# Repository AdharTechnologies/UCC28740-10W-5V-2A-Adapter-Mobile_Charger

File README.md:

# UCC28740-10W-5V-2A-Adapter-Mobile_Charger

1. Product page https://www.ti.com/product/UCC28740
2. Datasheet https://www.ti.com/lit/ds/symlink/ucc28740.pdf?ts=1782194478570&ref_url=https%253A%252F%252Fwww.ti.com%252Fproduct%252FUCC28740
3. Reference Design https://www.ti.com/lit/ug/sluual8/sluual8.pdf?ts=1782218864686&ref_url=https%253A%252F%252Fwww.ti.com%252Ftool%252FUCC28740EVM-525

#Note
This design was done for practice purpose it has not been tested

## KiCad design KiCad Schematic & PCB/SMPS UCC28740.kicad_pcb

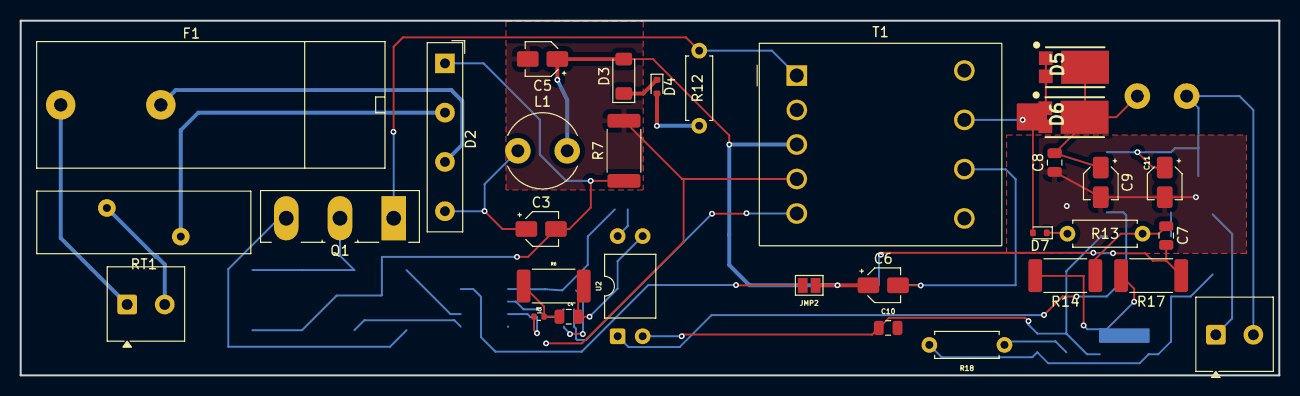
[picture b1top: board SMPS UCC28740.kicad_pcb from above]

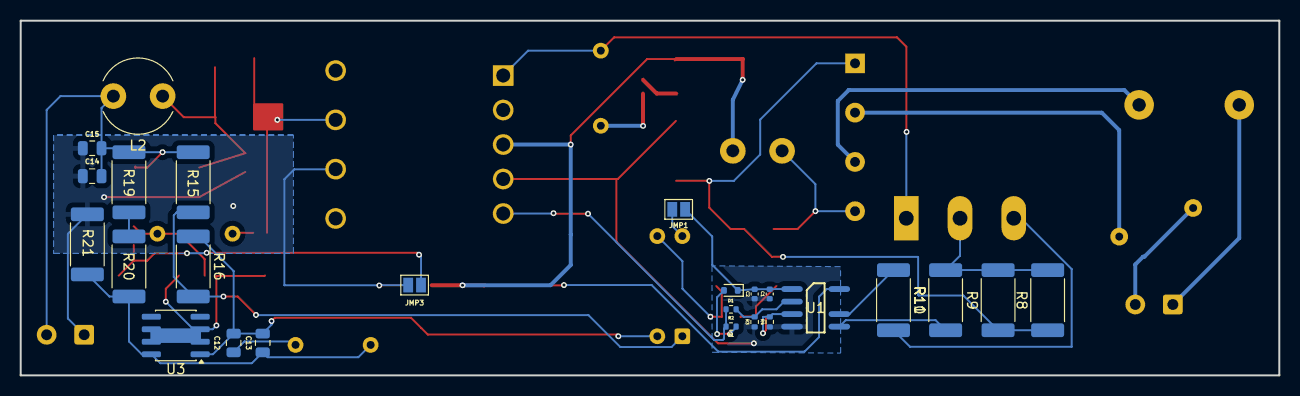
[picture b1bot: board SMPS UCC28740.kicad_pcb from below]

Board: 2 copper layers, 127.7 x 36.0 mm, 55 parts (25 on the bottom side), 35 nets.

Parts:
C1, C2: 2.2uF; C_0402_1005Metric
C3, C5: 6.8uF; CP_Elec_3x5.4
C4: 0.047uF; C_0805_2012Metric
C6: 100pF; CP_Elec_3x5.4
C7, C8, C10, C14, C15: 1uF; C_0805_2012Metric
C9, C11: 270uF; CP_Elec_3x5.4
C12: 4700pF; C_0805_2012Metric
C13: 2700pF; C_0805_2012Metric
D1: 200V,250mA; D_SOD-523
D2: 600V,0.8A; Diode_Bridge_19.0x3.5x10.0mm_P5.0mm
D3: 120V,600W; D_MiniMELF
D4: 1000V,1A; D_SOD-523
D5, D6: SBR10U45SP5-13; POWERDI5
D7: 75V,0.3A; D_SOD-523
F1: 2A,250V; Fuseholder_Cylinder-5x20mm_Bulgin_FX0457_Horizontal_Closed
JMP1, JMP2, JMP3: Jumper_2_Open; SolderJumper-2_P1.3mm_Open_Pad1.0x1.5mm
L1: 220uH; L_Radial_D7.5mm_P5.00mm_Fastron_07P
L2: 1uH; L_Radial_D7.5mm_P5.00mm_Fastron_07P
Q1: STU7NM60N; TO-247-3_Vertical
R1: 24.3; R_0402_1005Metric
R2: 105K; R_0402_1005Metric
R3: 27.4K; R_0402_1005Metric
R4: 22K; R_0402_1005Metric
R5: 0Ω,0.1W; R_0402_1005Metric
R6: 196K; R_2512_6332Metric_Pad1.40x3.35mm_HandSolder
R7: 0Ω, 0.125W; R_2512_6332Metric_Pad1.40x3.35mm_HandSolder
R8, R9: 1.87; R_2512_6332Metric_Pad1.40x3.35mm_HandSolder
R10: 0Ω,0.1W; R_2512_6332Metric_Pad1.40x3.35mm_HandSolder
R11: 1.29K; R_2512_6332Metric_Pad1.40x3.35mm_HandSolder
R12: 49.9; R_Axial_DIN0207_L6.3mm_D2.5mm_P7.62mm_Horizontal
R13: 820; R_Axial_DIN0207_L6.3mm_D2.5mm_P7.62mm_Horizontal
R14, R17: 0Ω, 0.1W; R_2512_6332Metric_Pad1.40x3.35mm_HandSolder
R15: 1.5K; R_2512_6332Metric_Pad1.40x3.35mm_HandSolder
R16: 1K; R_2512_6332Metric_Pad1.40x3.35mm_HandSolder
R18: 140K; R_Axial_DIN0207_L6.3mm_D2.5mm_P7.62mm_Horizontal
R19: 49.9; R_2512_6332Metric_Pad1.40x3.35mm_HandSolder
R20, R21: 42.2K; R_2512_6332Metric_Pad1.40x3.35mm_HandSolder
RT1: 10 Ω; RV_Disc_D21.5mm_W6.1mm_P7.5mm
T1: 560uH; T_Wurth_WE-FB-EE16_8_5
U1: UCC28740D; D0007A_N
U2: LTV‐817A; DIP-4_W10.16mm
U3: TL431D; SOIC-8_3.9x4.9mm_P1.27mm

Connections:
unnamed: C4.1, R6.2, U2.3
unnamed: C4.2, R5.2, R6.1
unnamed: C7.1, R13.2, R14.1
unnamed: C8.2, C9.1, D5.3, D6.3, L2.1
unnamed: C12.1, R18.1
unnamed: D1.2 (A), R1.1
unnamed: C1.1, C2.1, D1.1 (K), JMP1.1 (A), U1.1 (VDD)
unnamed: C3.1, D2.4 (+), L1.1
unnamed: C3.2, D2.1 (-), R7.1, R8.1, R9.1
unnamed: D2.2, RT1.2
unnamed: D2.3, F1.2
unnamed: C5.1, C6.1, D3.2 (A), JMP2.1 (A), L1.2, T1.3
unnamed: D3.1 (K), D4.1 (K)
unnamed: D4.2 (A), R12.1
unnamed: D5.1, D5.2, D6.1, D6.2, D7.2 (A), T1.8
unnamed: D7.1 (K), R13.1
unnamed: C11.1, C14.2, C15.2, L2.2, R15.2, R19.2
unnamed: JMP1.2 (B), U2.4
unnamed: JMP2.2 (B), U1.8 (HV)
unnamed: C7.2, JMP3.1 (A), R17.1
unnamed: Q1.1, R12.2, T1.1
unnamed: Q1.2, R8.2, R9.2, R11.2
unnamed: Q1.3, R10.2
unnamed: R14.2, R17.2, U3.2 (A), U3.3 (A), U3.6 (A), U3.7 (A)
unnamed: R15.1, R16.2, U2.1
unnamed: R19.1, R20.2
unnamed: R11.1, U1.5 (CS)
unnamed: R10.1, U1.6 (DRV)
unnamed: R4.2, R5.1, U1.3 (FB)
unnamed: R2.1, R3.2, U1.2 (VS)
unnamed: C10.1, C12.2, C13.2, R16.1, U2.2, U3.1 (K)
unnamed: C13.1, R18.2, R20.1, R21.2, U3.8 (REF)
PGND: C1.2, C2.2, C5.2, R3.1, R4.1, R7.2, T1.4, U1.4 (GND)
SGND: C6.2, C8.1, C9.2, C10.2, C11.2, C14.1, C15.1, JMP3.2 (B), R21.1, T1.7
VDD: R1.2, R2.2, T1.5

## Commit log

2026-06-23 README.md
